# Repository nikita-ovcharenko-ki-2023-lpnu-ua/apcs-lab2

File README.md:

# Лабораторна робота № 2 — AI-агент pcb-engineer

## Опис
Репозиторій містить AI-агента **pcb-engineer**, який автоматизовано проєктує
друковану плату в САПР **KiCad 10** за технічним завданням лабораторної роботи:
GUID з повного імені → п'ять квадратних компонентів → бібліотека → принципова
схема → плата форм-фактора кредитної картки → двошарове трасування (Freerouting)
→ ERC/DRC → Gerber RS-274X.

| Компонент | Шлях |
|---|---|
| Agent manifest | [`.github/agents/pcb-engineer.agent.md`](.github/agents/pcb-engineer.agent.md) |
| Skills (6) | [`.github/skills/`](.github/skills/) — `guid-params`, `kicad-library`, `kicad-schematic`, `kicad-pcb`, `autoroute`, `fab-output` |
| Commands (8) | [`.github/prompts/`](.github/prompts/) — `gen-params`, `create-library`, `create-schematic`, `create-pcb`, `route`, `fab`, `check`, `build-board` |
| Перевірка | [`.github/agent-tools/check.py`](.github/agent-tools/check.py) |
| Архітектура | [`docs/architecture.md`](docs/architecture.md) |
| Інструкція запуску | [`docs/usage.md`](docs/usage.md) |
| Докази перевірки | [`docs/verification.md`](docs/verification.md) |

## Гілки
- `develop` — лише агент з інструкціями;
- `feature/pcb-board` — результат запуску `/build-board`: скрипти, проєкт KiCad, CI;
- `master` — фінальний результат після перевірки.

## Запуск агента
**VS Code + GitHub Copilot Chat:** вибрати агента `pcb-engineer`, виконати
`/build-board fullName="Прізвище Ім'я По батькові"`.

**Claude Code:** `claude` у корені репозиторію, потім `/build-board fullName="…"`.

Потрібні KiCad 10 (`kicad-cli`, Python-модуль `pcbnew`) і Freerouting CLI — див. [`docs/usage.md`](docs/usage.md).

<!-- agent:project:start -->
## Плата

GUID: `24f9653f-a875-5d8f-9242-e476d2f1079a` (uuid5(NAMESPACE_DNS, full_name)).

| Компонент | Група GUID | Розмір, мм | Пінів |
|---|---|---|---|
| U1 | `24f9653f` | 8 × 8 | 8 |
| U2 | `a875` | 4 × 4 | 4 |
| U3 | `5d8f` | 4 × 4 | 4 |
| U4 | `9242` | 4 × 4 | 4 |
| U5 | `e476d2f1079a` | 12 × 12 | 12 |
| J1 | вільні піни | 1 × 4, крок 2.54 | 4 |

| Мережа | Піни |
|---|---|
| `N_2` | U1.1, U4.2, U4.4, U5.6 |
| `N_4` | U1.2, U4.3, U5.2 |
| `N_5` | U1.6, U2.4, U3.1 |
| `N_6` | U1.5, U5.4 |
| `N_7` | U2.3, U5.3, U5.10 |
| `N_8` | U2.2, U3.3 |
| `N_9` | U1.4, U4.1, U5.11 |
| `N_a` | U2.1, U5.12 |
| `N_d` | U3.2, U5.5 |
| `N_f` | U1.3, U1.8, U3.4, U5.7 |
| `FREE_U5_9` | U5.9, J1.1 |
| `FREE_U5_8` | U5.8, J1.2 |
| `FREE_U1_7` | U1.7, J1.3 |
| `FREE_U5_1` | U5.1, J1.4 |

Плата 85.6 × 53.98 мм, 2 шари. Проєкт KiCad — `hardware/lab2.kicad_pro`.
Відтворити: `python3 tools/params.py "<ПІБ>"`, `tools/library.py`, `tools/schematic.py`,
`tools/pcb.py`, `tools/route.py`, `tools/fab.py`; результат — `output/`.
<!-- agent:project:end -->

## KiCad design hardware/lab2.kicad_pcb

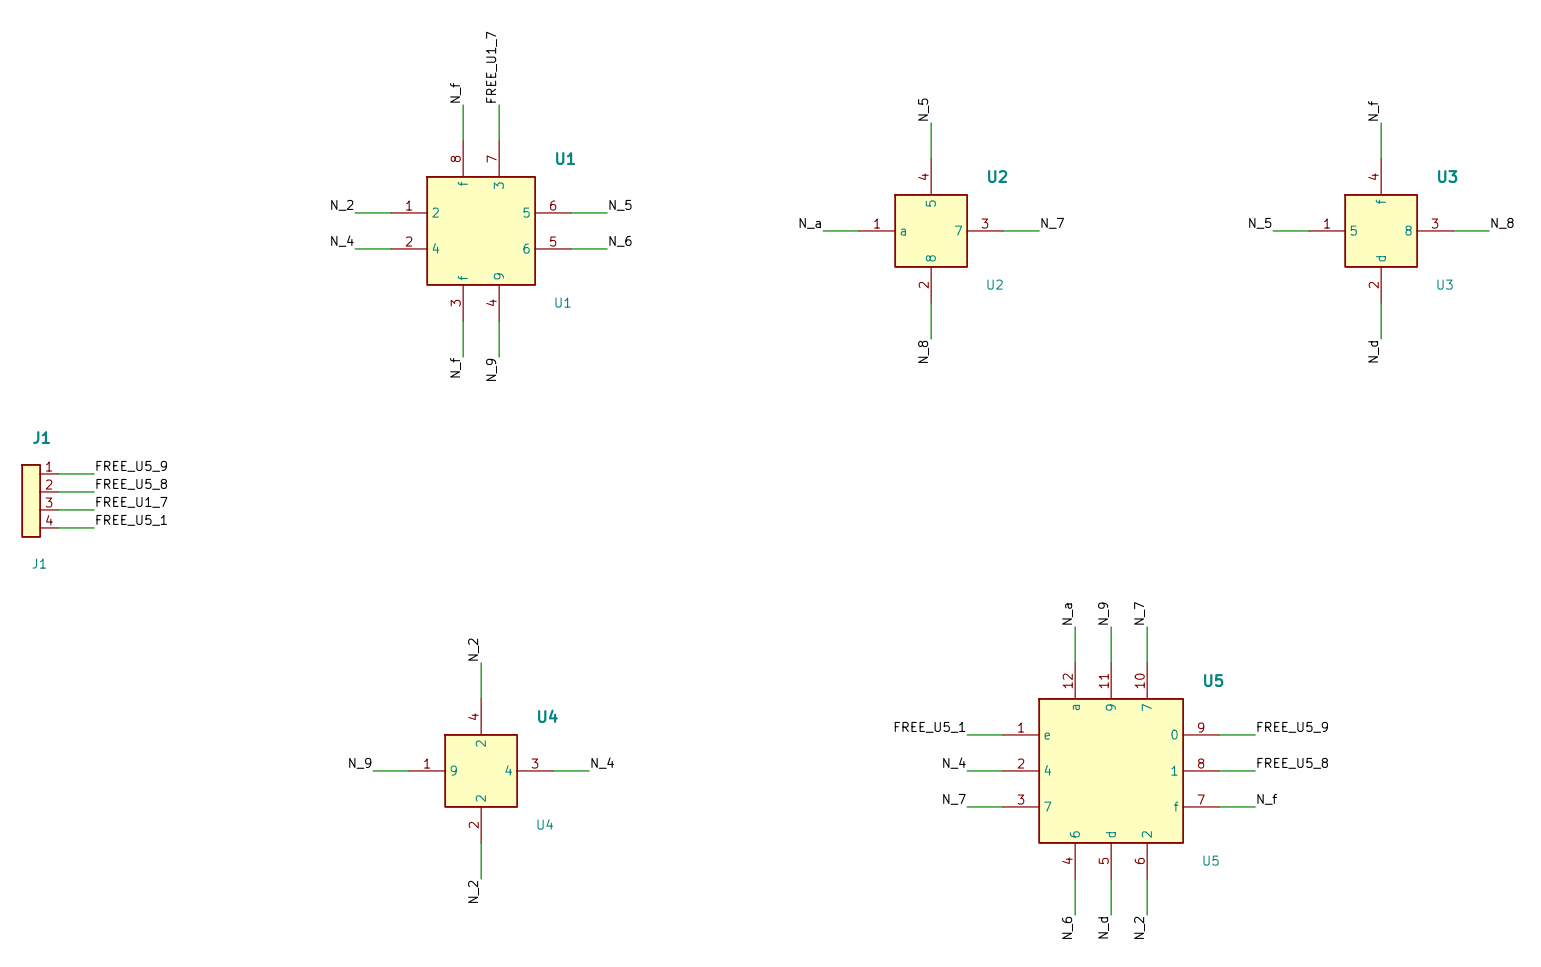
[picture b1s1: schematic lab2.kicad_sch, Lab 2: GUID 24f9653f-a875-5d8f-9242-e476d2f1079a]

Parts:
J1: J1; J1_1x04_P2.54mm
U1: U1; U1_8x8mm
U2: U2; U2_4x4mm
U3: U3; U3_4x4mm
U4: U4; U4_4x4mm
U5: U5; U5_12x12mm

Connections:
/FREE_U1_7: J1.3, U1.7 (3)
/FREE_U5_1: J1.4, U5.1 (e)
/FREE_U5_8: J1.2, U5.8 (1)
/FREE_U5_9: J1.1, U5.9 (0)
/N_2: U1.1 (2), U4.2, U4.4 (2), U5.6 (2)
/N_4: U1.2 (4), U4.3 (4), U5.2 (4)
/N_5: U1.6 (5), U2.4 (5), U3.1 (5)
/N_6: U1.5 (6), U5.4 (6)
/N_7: U2.3 (7), U5.3 (7), U5.10 (7)
/N_8: U2.2 (8), U3.3 (8)
/N_9: U1.4 (9), U4.1 (9), U5.11 (9)
/N_a: U2.1 (a), U5.12 (a)
/N_d: U3.2 (d), U5.5 (d)
/N_f: U1.3 (f), U1.8 (f), U3.4 (f), U5.7 (f)

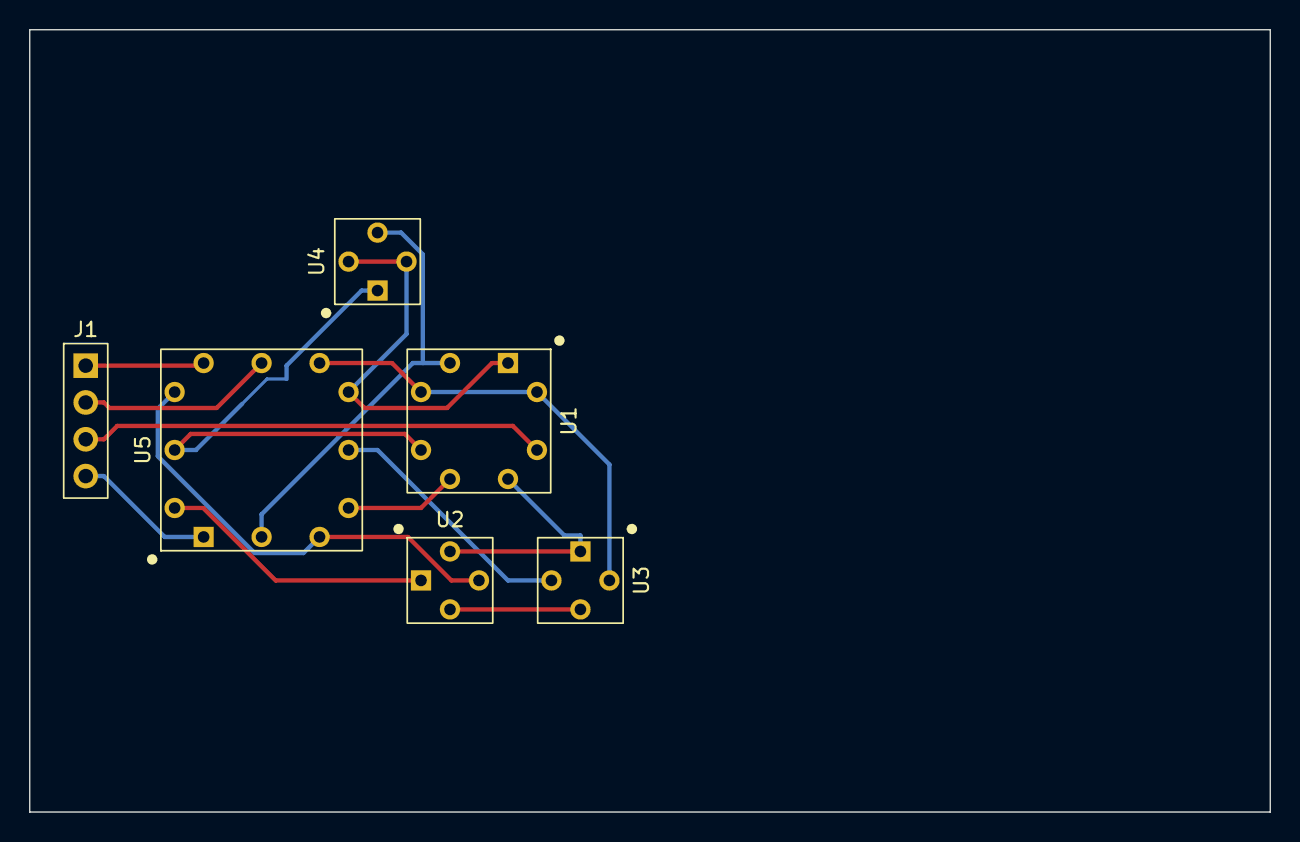
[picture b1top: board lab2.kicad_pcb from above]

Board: 2 copper layers, 85.6 x 54.0 mm, 6 parts (0 on the bottom side), 14 nets.
